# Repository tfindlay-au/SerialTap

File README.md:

# SerialTap

An open-hardware board that puts an appliance's 5 V serial service port on
Home Assistant. An ESP32-C3 with level translation, powered by the appliance
itself: one 4-wire cable carries 5 V, GND, TX and RX.

The reference target is a **Haier AS50QDFHRA** split-system air conditioner,
whose service port speaks GE Appliances **GEA3** at 230400 8N1
([docs/gea3.md](docs/gea3.md)). The board is not specialised to it: any
appliance exposing 5 V and a UART on a service connector is in scope.

## Status

**Version 1.0 has been sent to PCBWay; no board has been built yet.** The
`v1.0` tag marks the sources the order was built from.

Every design stage is done: power-path simulation, parts, library, schematic,
layout and three review gates. What is still owed is measurement on the real
appliance: the rail's current has so far been inferred, not measured
([ADR 0007](docs/adr/0007-rail-limit-inferred-not-measured.md)).

## The board

- **22 × 54 mm, 4-layer**, single-sided assembly, no mounting holes. It keeps
  the OEM module's outline and sits in its slot.
- **ESP32-C3-MINI-1** module. Programming and logs go over its built-in USB on
  a USB-C connector, so the appliance UART is never shared with logging.
- **Fixed-direction level translation** (TXU0204) between the 3.3 V module
  and the 5 V port, behind ESD protection and series resistors.
- **Power** from either the appliance or USB-C, ideal-diode OR-ed, through a
  current-limited eFuse and a 470 µF polymer bulk capacitor into a
  synchronous buck (TPS62162).

Service connector, as fitted to the reference appliance:

| Pin | 1 | 2 | 3 | 4 | 5 |
|---|---|---|---|---|---|
| Signal | 5 V | TX (board drives) | RX | spare (unknown) | GND |

## Where to start

| To understand… | Read |
|---|---|
| The vocabulary | [CONTEXT.md](CONTEXT.md) |
| The design, end to end | [docs/SPDD.md](docs/SPDD.md) |
| Why it is this way | [docs/adr/](docs/adr/): seven decisions, each with its context and what would reverse it |
| The protocol | [docs/gea3.md](docs/gea3.md) |
| How the schematic was checked | [docs/schematic-capture.md](docs/schematic-capture.md) |
| Layout rules and review gates | [docs/layout-rules.md](docs/layout-rules.md) |
| Parts and sourcing | [bom/README.md](bom/README.md) |
| Power-path simulation | [sim/README.md](sim/README.md) |
| Bring-up and measurement | [docs/bench-plan.md](docs/bench-plan.md), [docs/bench-results.md](docs/bench-results.md) |

## Repository layout

```
pcb/     KiCad 10 project: serialtap.kicad_sch / .kicad_pcb / .kicad_pro
lib/     the project's own symbols, footprints, 3D models and datasheets
sim/     LTspice power-path decks and their results
bom/     bill of materials and sourcing notes
docs/    design document, ADRs, protocol, layout and bench notes
bench/   capture and analysis scripts, and the ESPHome config used on the bench
```

## Opening and checking the design

Open `pcb/serialtap.kicad_pro` in **KiCad 10**. Everything it references is
in `lib/` through `${KIPRJMOD}`-relative paths, so it needs no global library.

```sh
CLI=/Applications/KiCad/KiCad.app/Contents/MacOS/kicad-cli   # macOS path
"$CLI" sch erc pcb/serialtap.kicad_sch
"$CLI" pcb drc --schematic-parity pcb/serialtap.kicad_pcb
```

The simulations need LTspice and vendor models that are not redistributed
here; [sim/README.md](sim/README.md) explains how to get them.

Fabrication outputs are regenerated rather than committed. Each fab order is
tagged, so a physical board traces back to its sources.

## Licence

Hardware under **CERN-OHL-P v2**; firmware and documentation under **MIT**.
Both are permissive. [NOTICE](NOTICE) sets out which files fall under which,
and the third-party material that falls under neither.

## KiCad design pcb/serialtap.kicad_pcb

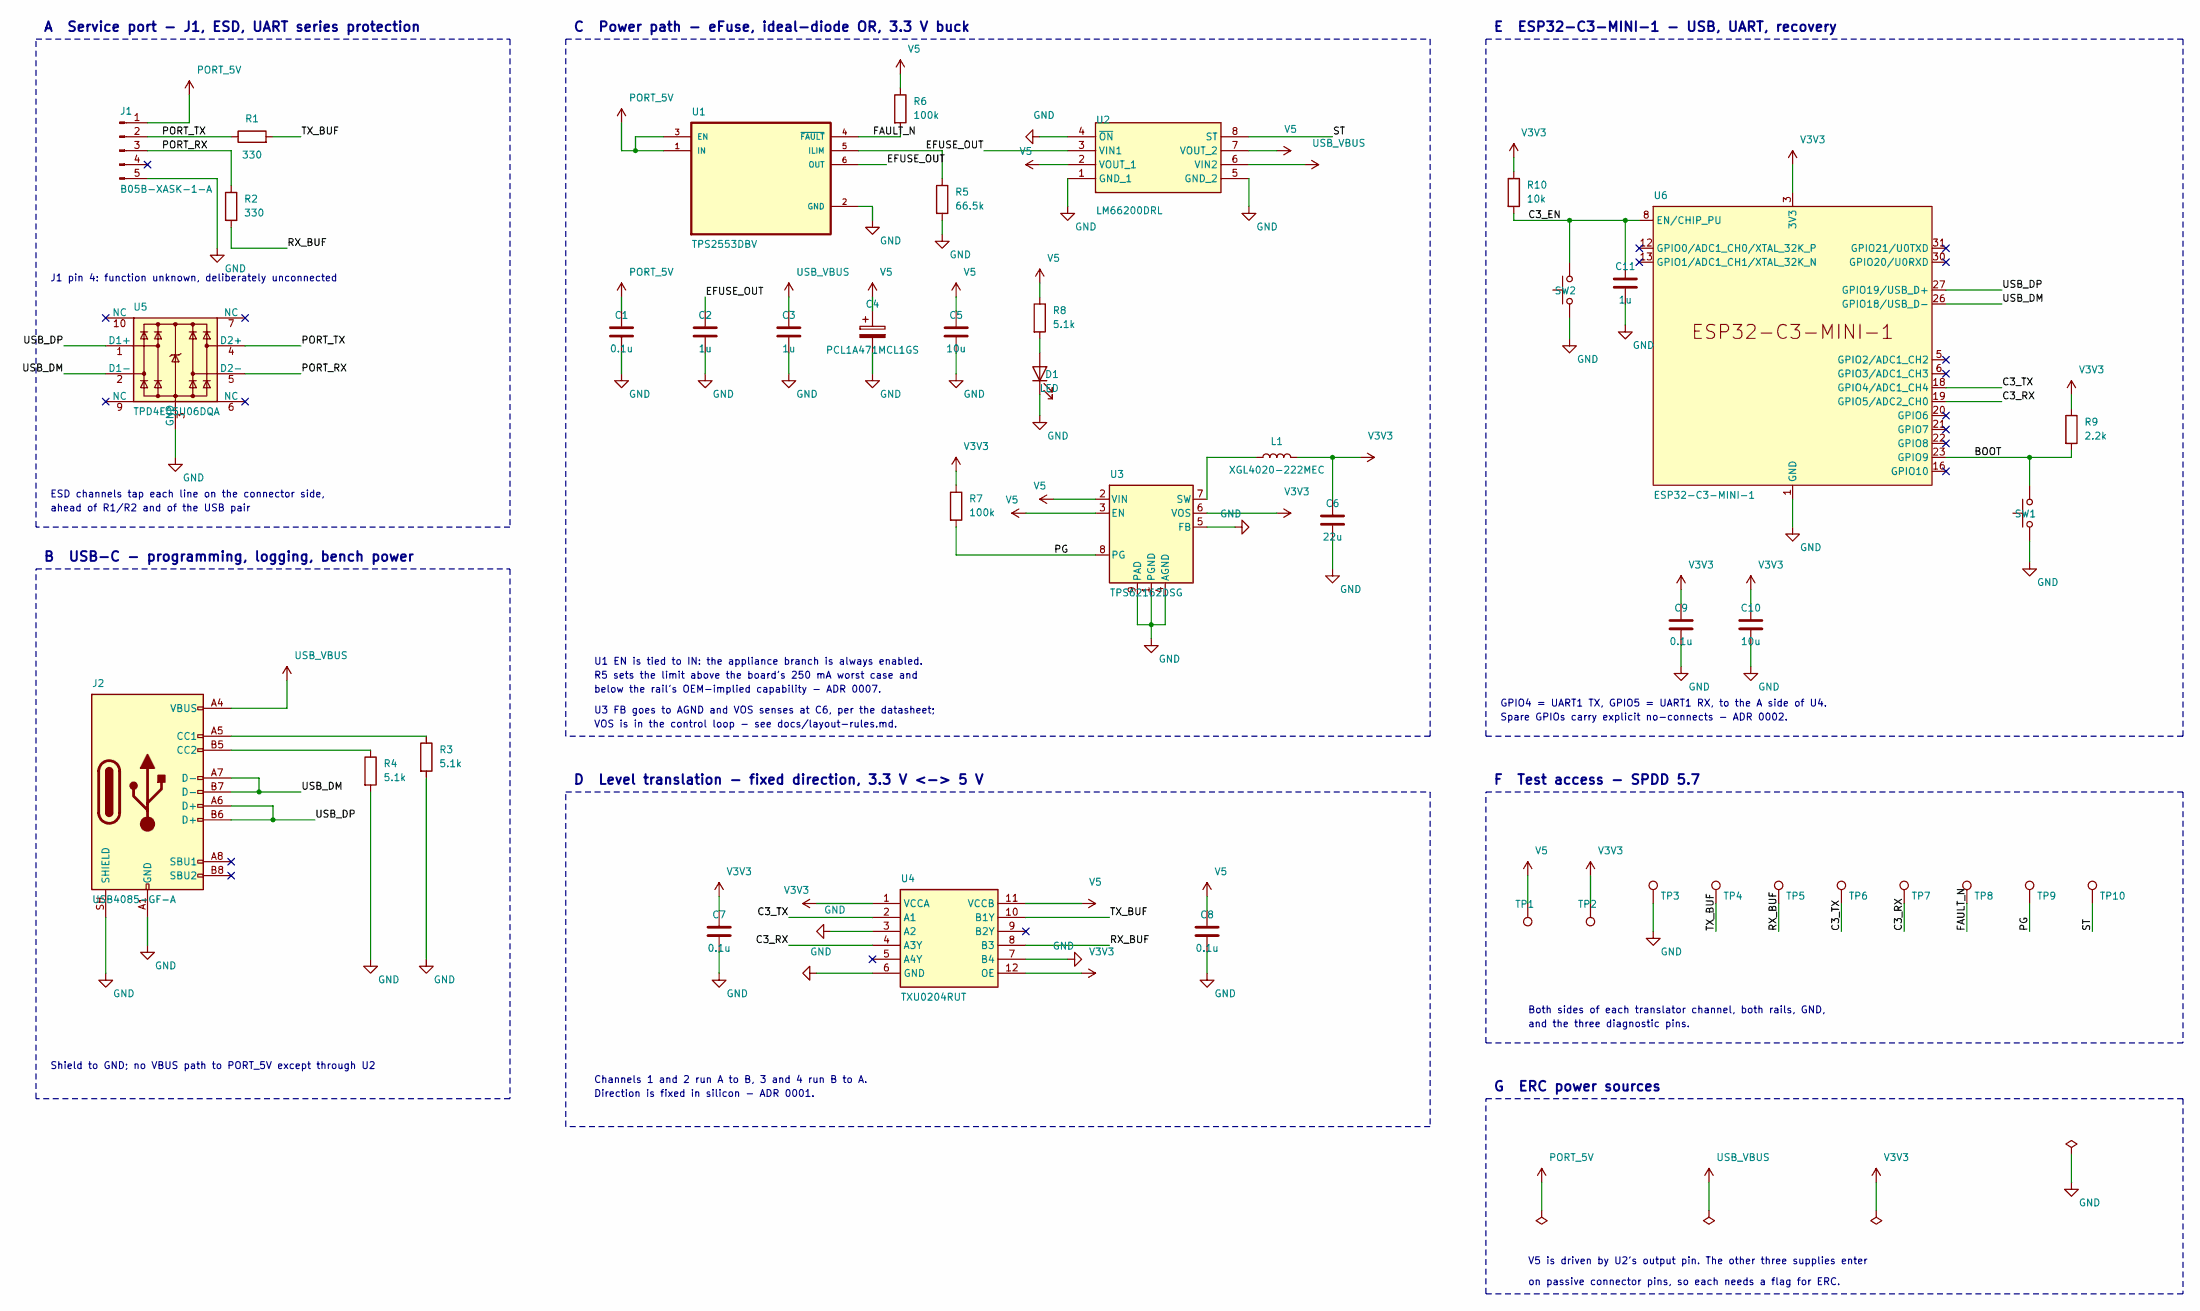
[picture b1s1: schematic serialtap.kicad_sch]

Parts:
C1, C7, C8, C9: 0.1u; C_0603_1608Metric; MPN CL10B104KB8NNNC
C2, C3, C11: 1u; C_0603_1608Metric; MPN CL10B105KA8NNNC
C4: PCL1A471MCL1GS; CP_Elec_8x10; MPN PCL1A471MCL1GS
C5, C10: 10u; C_1206_3216Metric; MPN CL31B106KAHNNNE
C6: 22u; C_1210_3225Metric; MPN CL32B226KAJNNNE
D1: LED; LED_0603_1608Metric; MPN LTST-C191KGKT
J1: B05B-XASK-1-A; JST_XA_B05B-XASK-1-A_1x05_P2.50mm_Vertical; MPN B05B-XASK-1-A(LF)(SN)
J2: USB4085-GF-A; USB_C_Receptacle_GCT_USB4085; MPN USB4085-GF-A
L1: XGL4020-222MEC; L_Coilcraft_XGL4020_4.0x4.0mm; MPN XGL4020-222MEC
R1, R2: 330; R_0603_1608Metric; MPN RK73H1JTTD3300F
R3, R4, R8: 5.1k; R_0603_1608Metric; MPN RK73H1JTTD5101F
R5: 66.5k; R_0603_1608Metric; MPN RK73H1JTTD6652F
R6, R7: 100k; R_0603_1608Metric; MPN RK73H1JTTD1003F
R9: 2.2k; R_0603_1608Metric; MPN RK73H1JTTD2201F
R10: 10k; R_0603_1608Metric; MPN RK73H1JTTD1002F
SW1, SW2: SW_Push; SW_Push_1P1T_NO_CK_KMR2; MPN KMR211NGLFS
TP1, TP2, TP3, TP4, TP5, TP6, TP7, TP8, TP9, TP10: TestPoint; TestPoint_Pad_D1.5mm
U1: TPS2553DBV; SOT-23-6; MPN TPS2553DBVR
U2: LM66200DRL; TI_DRL0008A_SOT-5X3-8_2.1x1.6mm_P0.5mm; MPN LM66200DRLR
U3: TPS62162DSG; Texas_DSG0008A_WSON-8-1EP_2x2mm_P0.5mm_EP0.9x1.6mm_ThermalV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; MPN TPS62162DSGT
U4: TXU0204RUT; TI_RUT0012A_UQFN-12_2.0x1.7mm_P0.4mm; MPN TXU0204RUTR
U5: TPD4E05U06DQA; USON-10_2.5x1.0mm_P0.5mm; MPN TPD4E05U06QDQARQ1
U6: ESP32-C3-MINI-1; MPN ESP32-C3-MINI-1-H4X

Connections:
/BOOT: R9.2, SW1.2, U6.23 (GPIO9)
/C3_EN: C11.1, R10.2, SW2.2, U6.8 (EN/CHIP_PU)
/C3_RX: TP7.1 (1_1), U4.4 (A3Y), U6.19 (GPIO5/ADC2_CH0)
/C3_TX: TP6.1 (1_1), U4.2 (A1), U6.18 (GPIO4/ADC1_CH4)
/EFUSE_OUT: C2.1, U1.6 (OUT), U2.3 (VIN1)
/FAULT_N: R6.2, TP8.1 (1_1), U1.4 (~FAULT)
/PG: R7.2, TP9.1 (1_1), U3.8 (PG)
/PORT_RX: J1.3, R2.1, U5.5 (D2-)
/PORT_TX: J1.2, R1.1, U5.4 (D2+)
/RX_BUF: R2.2, TP5.1 (1_1), U4.8 (B3)
/ST: TP10.1 (1_1), U2.8 (ST)
/TX_BUF: R1.2, TP4.1 (1_1), U4.10 (B1Y)
/USB_DM: J2.A7 (D-), J2.B7 (D-), U5.2 (D1-), U6.26 (GPIO18/USB_D-)
/USB_DP: J2.A6 (D+), J2.B6 (D+), U5.1 (D1+), U6.27 (GPIO19/USB_D+)
GND: C1.2, C2.2, C3.2, C4.2, C5.2, C6.2, C7.2, C8.2, C9.2, C10.2, C11.2, D1.1 (K), J1.5, J2.A1 (GND), J2.A12 (GND), J2.B1 (GND), J2.B12 (GND), J2.SH (SHIELD), R3.2, R4.2, R5.2, SW1.1, SW2.1, TP3.1 (1_1), U1.2 (GND), U2.1 (GND_1), U2.4 (~ON), U2.5 (GND_2), U3.1 (PGND), U3.4 (AGND), U3.5 (FB), U3.9 (PAD), U4.3 (A2), U4.6 (GND), U4.7 (B4), U5.3 (GND), U5.8 (GND), U6.1 (GND), U6.2 (GND), U6.11 (GND), U6.14 (GND), U6.36 (GND), U6.37 (GND), U6.38 (GND), U6.39 (GND), U6.40 (GND), U6.41 (GND), U6.42 (GND), U6.43 (GND), U6.44 (GND), U6.45 (GND), U6.46 (GND), U6.47 (GND), U6.48 (GND), U6.49 (GND), U6.50 (GND), U6.51 (GND), U6.52 (GND), U6.53 (GND)
unnamed: D1.2 (A), R8.2
unnamed: J2.A5 (CC1), R3.1
unnamed: J2.B5 (CC2), R4.1
unnamed: R5.1, U1.5 (ILIM)
unnamed: L1.1, U3.7 (SW)
PORT_5V: C1.1, J1.1, U1.1 (IN), U1.3 (EN)
USB_VBUS: C3.1, J2.A4 (VBUS), J2.A9 (VBUS), J2.B4 (VBUS), J2.B9 (VBUS), U2.6 (VIN2)
V3V3: C6.1, C7.1, C9.1, C10.1, L1.2, R7.1, R9.1, R10.1, TP2.1 (1_1), U3.6 (VOS), U4.1 (VCCA), U4.12 (OE), U6.3 (3V3)
V5: C4.1, C5.1, C8.1, R6.1, R8.1, TP1.1 (1_1), U2.2 (VOUT_1), U2.7 (VOUT_2), U3.2 (VIN), U3.3 (EN), U4.11 (VCCB)

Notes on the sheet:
D Level translation - fixed direction, 3.3 V <-> 5 V
Channels 1 and 2 run A to B, 3 and 4 run B to A.
below the rail's OEM-implied capability - ADR 0007.
U1 EN is tied to IN: the appliance branch is always enabled.
Spare GPIOs carry explicit no-connects - ADR 0002.
A Service port - J1, ESD, UART series protection
R5 sets the limit above the board's 250 mA worst case and
V5 is driven by U2's output pin. The other three supplies enter
on passive connector pins, so each needs a flag for ERC.
VOS is in the control loop - see docs/layout-rules.md.
GPIO4 = UART1 TX, GPIO5 = UART1 RX, to the A side of U4.
C Power path - eFuse, ideal-diode OR, 3.3 V buck
and the three diagnostic pins.
F Test access - SPDD 5.7
Both sides of each translator channel, both rails, GND,
ahead of R1/R2 and of the USB pair
ESD channels tap each line on the connector side,
E ESP32-C3-MINI-1 - USB, UART, recovery
U3 FB goes to AGND and VOS senses at C6, per the datasheet;
Shield to GND; no VBUS path to PORT_5V except through U2
J1 pin 4: function unknown, deliberately unconnected
G ERC power sources
Direction is fixed in silicon - ADR 0001.
B USB-C - programming, logging, bench power

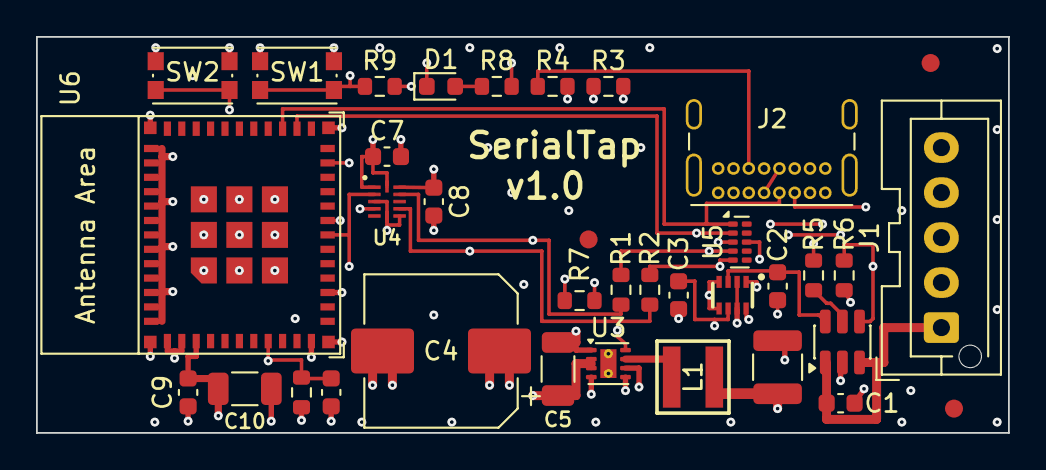
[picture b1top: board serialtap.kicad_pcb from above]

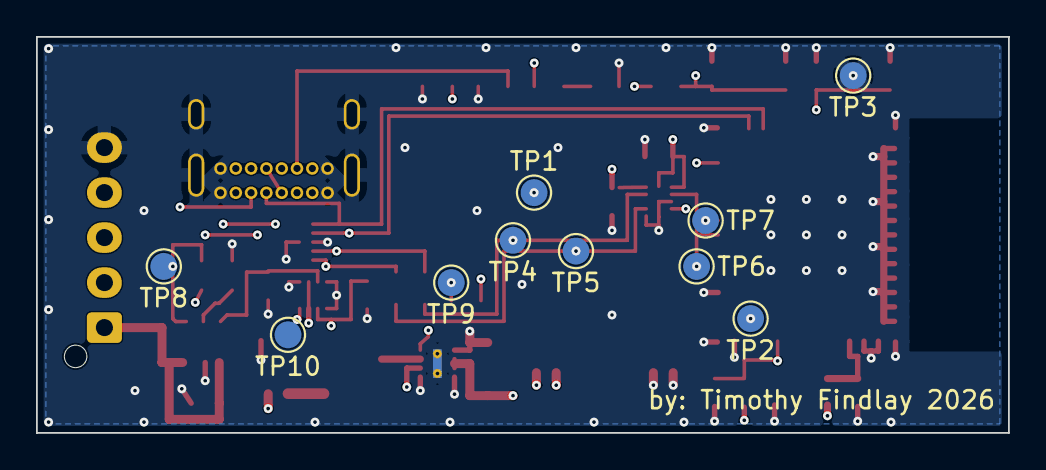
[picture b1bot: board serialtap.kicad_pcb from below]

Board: 4 copper layers, 54.0 x 22.0 mm, 46 parts (10 on the bottom side), 24 nets.

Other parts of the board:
FID1, FID2, FID3: Fiducial_1mm_Mask2mm

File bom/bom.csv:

Reference,Qty,Value,Footprint,MPN,Manufacturer,DigiKey_PN,DigiKey_Stock,Mouser_PN,Mouser_Stock,LCSC_PN,LCSC_Stock,Chosen_Distributor,Unit_Price_USD,Price_Basis,Validated,DNP,Notes
C4,1,PCL1A471MCL1GS,serialtap:CP_Elec_8x10,PCL1A471MCL1GS,Nichicon,PCL1A471MCL1GS-ND,0,647-PCL1A471MCL1GS,69,,0,Mouser,2.1300,Mouser AU A$3.25,no,no,"SINGLE SOURCE, THIN. Mouser 69 in stock (user-checked 2026-09-20, A$3.25). DigiKey non-stock: 24-week lead, MOQ 500. Not listed at LCSC. Mouser PN unverified — 647- prefix assumed, confirm at order. Buy spares now"
C6,1,22u,serialtap:C_1210_3225Metric,CL32B226KAJNNNE,Samsung Electro-Mechanics,,,,,C309062,30185,LCSC,0.3599,LCSC indicative,no,no,Value and dielectric per TPS62162 datasheet; 25 V for bias headroom at 3.3 V
"C1,C7,C8,C9",4,0.1u,serialtap:C_0603_1608Metric,CL10B104KB8NNNC,Samsung Electro-Mechanics,,,,,C1591,268519,LCSC,0.0115,LCSC indicative,no,no,"Murata GRM188R71H104KA93D is a drop-in second source, 318k in stock"
"C5,C10",2,10u,serialtap:C_1206_3216Metric,CL31B106KAHNNNE,Samsung Electro-Mechanics,,,,,C14860,30509,LCSC,0.2660,LCSC indicative,no,no,"25 V part on a 5 V rail, chosen for DC-bias headroom (inference, not a vendor curve)"
"C2,C3,C11",3,1u,serialtap:C_0603_1608Metric,CL10B105KA8NNNC,Samsung Electro-Mechanics,,,,,C29936,178930,LCSC,0.0218,LCSC indicative,no,no,
D1,1,LED,serialtap:LED_0603_1608Metric,LTST-C191KGKT,Lite-On,,,,,C125098,193281,LCSC,0.0217,LCSC indicative,no,no,Vf 1.9-2.4 V gives ~0.6 mA through R8. Dim by design (SPDD 5.7). -55..+85 C
J1,1,B05B-XASK-1-A,serialtap:JST_XA_B05B-XASK-1-A_1x05_P2.50mm_Vertical,B05B-XASK-1-A(LF)(SN),JST,455-B05B-XASK-1-A-ND,5457,,,C491708,4064,DigiKey,0.2620,DK qty10,no,no,Through-hole — needs the selective/hand-solder step
J2,1,USB4085-GF-A,serialtap:USB_C_Receptacle_GCT_USB4085,USB4085-GF-A,GCT,2073-USB4085-GF-ATR-ND,72058,,,C7095263,2167,DigiKey,0.7720,DK qty10,no,no,"Through-hole, shares the JST solder step"
L1,1,XGL4020-222MEC,serialtap:L_Coilcraft_XGL4020_4.0x4.0mm,XGL4020-222MEC,Coilcraft,2457-XGL4020-222MEC-ND,3876,,,C6012410,5408,LCSC,1.3630,LCSC indicative,no,no,"DigiKey lists it as Marketplace: +$10 flat shipping, ~4 day. Coilcraft direct is the other option"
"R1,R2",2,330,serialtap:R_0603_1608Metric,RK73H1JTTD3300F,KOA Speer,,,,,C160038,3017,LCSC,0.0051,LCSC indicative,no,no,"One KOA RK73H series across all five resistor values: 1%, 100ppm/degC, -55..+155 C"
R5,1,66.5k,serialtap:R_0603_1608Metric,RK73H1JTTD6652F,KOA Speer,,,,,C2480277,2192,LCSC,0.0154,LCSC indicative,no,no,"RILIM. 1% is a TPS2553 datasheet requirement, not a preference"
"R6,R7",2,100k,serialtap:R_0603_1608Metric,RK73H1JTTD1003F,KOA Speer,,,,,C130231,11115,LCSC,0.0043,LCSC indicative,no,no,
"R3,R4,R8",3,5.1k,serialtap:R_0603_1608Metric,RK73H1JTTD5101F,KOA Speer,,,,,C160048,13741,LCSC,0.0076,LCSC indicative,no,no,
R9,1,2.2k,serialtap:R_0603_1608Metric,RK73H1JTTD2201F,KOA Speer,,,,,C130233,1033,LCSC,0.0045,LCSC indicative,no,no,"Not 10k: sized so SW1 carries 1.5 mA, above C&K's 1 mA minimum contact current"
R10,1,10k,serialtap:R_0603_1608Metric,RK73H1JTTD1002F,KOA Speer,,,,,C130232,1192,LCSC,0.0038,LCSC indicative,no,no,"Thinnest line of the new passives at 1,192 - still ~100 boards"
"SW1,SW2",2,SW_Push,serialtap:SW_Push_1P1T_NO_CK_KMR2,KMR211NGLFS,C&K (Littelfuse),,,,,C221676,8125,LCSC,0.6362,LCSC indicative,no,no,"NG = no ground pin, per the C&K ordering key - fixes the footprint choice. Silver contacts, -40..+85 C"
U1,1,TPS2553DBV,serialtap:SOT-23-6,TPS2553DBVR,Texas Instruments,296-32464-1-ND,0,595-TPS2553DBVR,882,C55266,44248,LCSC,0.2979,LCSC indicative,no,no,"NON-LATCHING part — NOT the -1. DigiKey out of stock, 3000 due 2026-10-26. Dual-sourced: Mouser also has 882 at A$1.60 (user-checked 2026-09-20), so LCSC price vs Mouser second source. Mouser PN unverified — 595- prefix assumed. Verify marking on receipt: LCSC's auto-generated description lists latch protection, which is family boilerplate, not this suffix"
U2,1,LM66200DRL,serialtap:TI_DRL0008A_SOT-5X3-8_2.1x1.6mm_P0.5mm,LM66200DRLR,Texas Instruments,296-LM66200DRLRCT-ND,83454,,,C3235556,26447,DigiKey,0.4160,DK qty10,no,no,Both OR branches in one package
U3,1,TPS62162DSG,serialtap:Texas_DSG0008A_WSON-8-1EP_2x2mm_P0.5mm_EP0.9x1.6mm_ThermalVias,TPS62162DSGT,Texas Instruments,296-29897-1-ND,6663,,,C2863597,349,LCSC,1.5049,LCSC indicative,no,no,"DSGR (3000 reel) is $0.97 at LCSC / $1.86 DK qty1 — same die, reel size only"
U4,1,TXU0204RUT,serialtap:TI_RUT0012A_UQFN-12_2.0x1.7mm_P0.4mm,TXU0204RUTR,Texas Instruments,296-TXU0204RUTRCT-ND,767,,,C5217875,301,DigiKey,0.8440,DK qty10,no,no,Thinnest stock of any line at both sources. RUT package only
U5,1,TPD4E05U06DQA,serialtap:USON-10_2.5x1.0mm_P0.5mm,TPD4E05U06QDQARQ1,Texas Instruments,296-40696-1-ND,77999,,,,0,DigiKey,0.7930,DK qty10,no,no,DigiKey only. LCSC carries the -Q1 solely as -ES engineering samples (C19170925) — not orderable for a build. Non-Q1 TPD4E05U06DQAR is plentiful at LCSC but drops the temperature grade SPDD 7.4 bought
U6,1,ESP32-C3-MINI-1,serialtap:ESP32-C3-MINI-1,ESP32-C3-MINI-1-H4X,Espressif Systems,1904-ESP32-C3-MINI-1-H4XTR-ND,0,,,C41349510,911,LCSC,3.0795,LCSC indicative,no,no,"LCSC only. DigiKey non-stock: 4-week lead, 3250-piece reel. H = 105C grade and X = rev v1.1 are both mandatory (SPDD 7.4) — do not accept -N4 or a non-X substitution"

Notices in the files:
pcb/serialtap.kicad_sch:
Copyright 2026 Timothy Findlay. Licensed under CERN-OHL-P v2.
Distributed WITHOUT ANY EXPRESS OR IMPLIED WARRANTY. See LICENSE and NOTICE.
